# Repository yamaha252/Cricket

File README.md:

# Cricket

Лёгкий BLE-маячок для поиска упавшего FPV-дрона (`cricket-tag`), своё приложение для поиска и, на следующем этапе, приёмник для поискового дрона (`cricket-seeker`).

Маячок спроектирован с нуля на модуле Insight SiP ISP2454-LX (Nordic nRF54L15, D-29). Схема и плата готовы, прошивка и приложение написаны и собираются; платы ещё не заказаны, поэтому на железе ничего не проверено.

## Что умеет cricket-tag

- Ставится на дроны от BetaFPV Pavo Pico II (80 мм) и крупнее, весит около 3 г с аккумулятором.
- Заряжается от 5 В полётника, после падения работает от своего Li-Po: бипер часами, BLE по расчёту 3,5–6,5 недели (ток ещё не измерен).
- Сам отличает падение от замены аккумулятора: статус armed по MSP, удар по акселерометру, нарастающая тревога. Тревогу поднимает и аварийный конец полёта при живых 5 В: failsafe, дизарм в воздухе, перезагрузка полётника, потеря связи с пультом (D-35, D-36).
- Пищит с тумблера BEEPER в Betaflight и по команде из приложения; пока маячок в тревоге, команду «пищи» принимает и чужой телефон — помощник может найти дрон по звуку.
- Виден своему приложению на сотни метров: Coded PHY, ориентир 300–500 м при прямой видимости, на 1M — 150–250 м (D-17). В рекламе — последние координаты GPS полётника и их возраст.
- Молчит в эфире, пока дрон armed, чтобы не мешать ELRS 2,4 ГГц (D-37).
- Громкий бипер уровня Flywoo Finder V1.0 и белый светодиод.
- Обновляется по BLE (MCUboot, подписанные образы), управляется только привязанным телефоном.
- Собирается на заводе целиком, руками только прошивка и пайка проводов аккумулятора и полётника к площадкам (D-26).

Сети Apple Find My и Google Find Hub — следующий этап после своего механизма поиска (D-32, D-33), сейчас их нет ни в прошивке, ни в приложении.

## Схема и плата

Ревизия A: 17 × 32 мм, 2 слоя, 0,6 мм, все детали сверху. Подробности — в [hardware/cricket-tag/README.md](hardware/cricket-tag/README.md).

Слева направо: верх, низ с площадками проводов и SWD, медь обоих слоёв. Модуль ISP2454-LX (вверху слева, у антенны) и излучатель (большой прямоугольник внизу) на рендере не показаны: у них нет 3D-моделей, видны только площадки.

## Документация

| Документ | Содержание |
|---|---|
| [docs/requirements.md](docs/requirements.md) | требования |
| [docs/decisions.md](docs/decisions.md) | журнал решений с причинами (D-1…D-41) |
| [docs/concept.md](docs/concept.md) | архитектура, режимы, признаки падения, радио, энергобюджет |
| [docs/protocol.md](docs/protocol.md) | реклама Cricket, интервалы по режимам, сервис GATT, команды, привязка |
| [docs/components.md](docs/components.md) | компоненты, коды LCSC, номиналы, требования к антенне, масса |
| [docs/manufacturing.md](docs/manufacturing.md) | заводская сборка, варианты заводов, порядок заказа |
| [docs/cost.md](docs/cost.md) | себестоимость: расчёты заводов и оценка по тиражам |
| [docs/module-options.md](docs/module-options.md) | радиомодули со склада JLCPCB и голый nRF54L10 (отклонены) |
| [docs/app.md](docs/app.md) | своё приложение, сети Find My и Find Hub |
| [docs/setup.md](docs/setup.md) | окружение разработки |

## Состав репозитория

| Папка | Назначение | Статус |
|---|---|---|
| [`hardware/cricket-tag/`](hardware/cricket-tag/README.md) | KiCad-проект маячка | схема ревизии A (ERC 0) и плата 17 × 32 мм (DRC 0) готовы и прошли ревью (D-40, D-41); выходные файлы для завода — в `fab/` |
| [`hardware/cricket-seeker/`](hardware/cricket-seeker/README.md) | приёмник для поискового дрона | не начат |
| [`firmware/`](firmware/README.md) | своя прошивка под MIT, Zephyr / nRF Connect SDK v3.4.2 | свой механизм поиска написан, собирается под плату и nRF54L15 DK; на железе не запускалась |
| [`app/`](app/README.md) | приложение на Flutter: Android и iOS | сканер, «тепло-холодно», карта с пеленгом, офлайн-карты, привязка и настройки есть; с настоящим маячком не проверено |
| `docs/` | документация | актуальна |

## Статус

На 2026-11-12.

**Плата.** Схема и плата ревизии A готовы: ERC 0, DRC со сверкой со схемой 0, разводка убрана и проверена (D-40, D-41). Gerber, BOM и CPL делает `hardware/cricket-tag/make_fab.sh`.

**Заказ.** Завод для первого заказа не выбран (D-31), ничего не оплачено. Рекомендованная нулевая партия — 3–4 платы. Расчёты, прошедшие проверку заводов:

| Завод | Партия | К оплате |
|---|---|---|
| SCSPCBA | 4 платы | 159,83 $ |
| NextPCB | 8 плат | 371 $ |
| Seeed Fusion | 8 плат | 520,70 $ (~470 $ с купоном) |

JLCPCB (~250–285 $ за 8 плат) скрывает сборку для Казахстана и делает панели только с V-cut, который плате не подходит. В серии оценка ~20–22 $ за плату при 24 шт. и ~15–17 $ при 120 шт. Подробности — [docs/manufacturing.md](docs/manufacturing.md#варианты-заводов) и [docs/cost.md](docs/cost.md).

**Прошивка.** Наборы рекламы Cricket Coded и 1M, сервис GATT, режимы, бипер, кнопка, клиент MSP, удар по LIS2DH12, привязка, настройки Bluetooth из приложения, MCUboot с обновлением по BLE, сторожевой таймер, сборка с низким потреблением. Не сделано: замер тока, шлюз Bluetooth → MSP для Betaflight Configurator, наборы Apple и Google ([firmware/README.md](firmware/README.md#не-сделано)).

**Приложение.** Свой BLE-слой на Kotlin и Swift, всё работает без сети. Не сделано: обновление прошивки по BLE, фоновое сканирование, сети Find My и Find Hub, подпись сборок ([app/README.md](app/README.md#не-сделано)).

**Дальше:** выбрать завод и заказать платы, проверить прошивку на nRF54L15 DK, затем на плате вместе с приложением, измерить ток.

## Лицензия

[MIT](LICENSE): схема, плата, скрипты, прошивка, приложение и документация.

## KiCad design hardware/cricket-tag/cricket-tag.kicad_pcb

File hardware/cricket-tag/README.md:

# cricket-tag

KiCad-проект маячка. Готовы библиотека проекта и схема ревизии A на модуле ISP2454-LX (D-29; ERC: 0 ошибок, 0 предупреждений). Плата 17 × 32 мм разведена полностью, убрана (D-40) и прошла ревью схемы и разводки (D-41): DRC со сверкой со схемой — 0 нарушений, 0 неподключённых, вся земля связна. Как она разведена — раздел «Разводка», картинки текущей платы — `render/`: [схема](render/schematic.png), [верх](render/3d-top.png), [низ](render/3d-bottom.png), [медь](render/copper-top-bottom.png). Картинки платы — `kicad-cli pcb render --side top|bottom` и `kicad-cli pcb export svg` слоёв F.Cu и B.Cu. Картинку схемы после правок пересобирают: `kicad-cli sch export pdf` с `--exclude-drawing-sheet`, затем `pdftoppm -png -r 130 -singlefile`. Минимумы DRC под JLCPCB 2 слоя (дорожка 0,1 мм, зазор 0,127 мм, via от 0,45/0,3 мм с кольцом 0,1 мм, медь до кромки 0,2 мм; классы цепей — в разделе «Разводка»), стек 0,6 мм FR4, ENIG.

## Параметры платы, ревизия A

- 17 × 32 мм (см. «Размер платы» и «Разводка», D-29), 2 слоя, 0,6 мм.
- Все компоненты сверху, плата собирается заводом целиком. Снизу только медные площадки под провода и SWD (D-26): [docs/manufacturing.md](../../docs/manufacturing.md).
- Модуль Insight SiP ISP2454-LX (nRF54L15, D-29) в углу платы на дальнем конце от хвоста, антенной половиной к торцу: в 1 мм от торцевой кромки и в 1,3 мм от боковой (datasheet: 1 мм; +0,3 мм под дорожки VDD и SWD). У торца полоса 14 × 5 мм без меди на обоих слоях. Подробности в [docs/components.md](../../docs/components.md#требования-к-встроенной-антенне).
- Аккумулятор снизу, до 15 мм длиной вместе с платой защиты, провода паяются к J2.

## Порядок работы над схемой

1. ~~Символ и футпринт модуля~~ — готово: ISP2454-LX (D-29), см. раздел «Библиотека».
2. ~~Вход 5 В, VIN_SENSE, TP4054, площадки аккумулятора, делитель VBAT, LDO~~ — готово, см. раздел «Схема». Площадки полётника J1 нарисованы здесь же, резисторы UART — на шаге 6.
3. ~~Модуль, площадки SWD~~ — готово, карта выводов ниже (D-29). Кварц и развязка модуля с D-29 внутри ISP2454-LX. TC2030-NL заменён четырьмя площадками J3 (D-26).
4. ~~PAM8904E и излучатель~~ — готово, излучатель CPT-1117-83 (D-27), см. «Размер платы».
5. ~~Светодиод с ключом от VBAT, кнопка, LIS2DH12~~ — готово, см. «Схема».
6. ~~Резисторы 1 кОм в UART между площадками полётника и модулем~~ — готово.
7. ~~Поле `LCSC Part` в каждом символе~~ — заполнено у всех деталей в BOM: 20 уникальных позиций (после D-29 ушли кварц и конденсаторы 18 пФ). Без него только площадки J1–J3 (`in_bom no`).
8. ~~ERC до нуля ошибок~~ — 0 ошибок, 0 предупреждений.

Плата с ISP2454-LX разведена (см. «Разводка»). Выходные файлы делает `make_fab.sh` (в `fab/`), по ним 2026-11-10 получены расчёты JLCPCB (D-30) и NextPCB (D-31), см. [docs/cost.md](../../docs/cost.md). После уборки меди D-40 (2026-11-12) gerber изменились, BOM и CPL прежние: перед оплатой любого из расчётов загрузить новый `cricket-tag-gerbers.zip`. Завод для первого заказа не выбран, варианты сравниваются ([docs/manufacturing.md](../../docs/manufacturing.md#варианты-заводов)). Медь местами ближе 0,4 мм к краю, поэтому панель только с фрезеровкой и mouse bites, не V-cut; разделяет завод (D-31).

Компоненты: [docs/components.md](../../docs/components.md). Заметки по схеме: [docs/concept.md](../../docs/concept.md#заметки-для-схемы).

## Схема

`cricket-tag.kicad_sch` строит скрипт `gen_schematic.py` по шагам из списка выше. Каждый вывод подключён коротким проводом к метке цепи или к символу питания. Источник схемы — скрипт: ручные правки в KiCad пропадут при следующем запуске. Когда схема будет готова и её начнут править в KiCad, файл схемы станет основным, а скрипт — историей.

```bash
python3 hardware/cricket-tag/gen_schematic.py
kicad-cli sch erc hardware/cricket-tag/cricket-tag.kicad_sch -o /tmp/erc.rpt
```

Если в KiCad не настроены глобальные таблицы библиотек (их создаёт первый запуск KiCad), ERC сообщает «library not included». Тогда ERC запускают с переменной `KICAD_CONFIG_HOME`: она указывает на каталог `10.0/` с копиями `sym-lib-table` и `fp-lib-table` из `/Applications/KiCad/KiCad.app/Contents/SharedSupport/template/`.

Узел питания (шаг 2):

| Цепь | Что на ней |
|---|---|
| +5V | J1.1 (полётник), анод D1 B5819W, верх делителя VIN_SENSE |
| VCHG | катод D1, C1 10 мкФ, TP4054 VCC |
| VBAT | TP4054 BAT, C2 1 мкФ, J2.1 (аккумулятор), делитель VBAT, вход и EN LDO, C4 1 мкФ |
| +3V3 | выход TPS7A0233, C5 1 мкФ |
| VIN_SENSE | R1 1 МОм / R2 1,5 МОм (D-23) → GPIO модуля |
| VBAT_SENSE | R4 / R5 по 1 МОм, C3 100 нФ → АЦП модуля |
| CHRG_N | открытый сток TP4054 → GPIO с внутренней подтяжкой |
| PROG | R3 22 кОм: ток заряда ≈ 45 мА |

Модуль (шаг 3, D-29): U1 ISP2454-LX — кварцы 32 МГц и 32,768 кГц, DC/DC и развязка VDD внутри модуля, поэтому C6–C9 и Y1 из прежней схемы нет (позиционные обозначения не перенумерованы). Площадки SWD J3: 1 VDD, 2 SWDIO, 3 SWCLK, 4 GND (только медь снизу, `in_bom no`, D-26). OUT_MOD соединён с OUT_ANT; ~RESET (подтяжка внутри) и неиспользуемые GPIO помечены «не подключено».

Карта выводов модуля (D-29):

| Площадка | Порт | Цепь | Примечание |
|---|---|---|---|
| 32 | P0.02 | UART_TX | UARTE30 → RX полётника через 1 кОм (шаг 6) |
| 29 | P0.00 | UART_RX | UARTE30 ← TX полётника через 1 кОм. **Внутренняя** площадка: переходное под модулем, закрытое маской |
| 34 | P0.03 | VIN_SENSE | есть ли 5 В (цифровой вход, D-23), пробуждение из System OFF |
| 36 | P1.07/AIN3 | VBAT_SENSE | АЦП |
| 38 | P1.05 | BUTTON | кнопка на GND, внутренняя подтяжка, пробуждение |
| 40 | P1.04 | BUZ_DIN | PWM20, 3–8 кГц на PAM8904E |
| 42 | P2.05 | BUZ_EN1 | режим PAM8904E |
| 44 | P2.04 | CHRG_N | внутренняя подтяжка; читается опросом (на P2 нет прерываний) |
| 48 | P1.11 | ACC_INT1 | прерывание LIS2DH12, пробуждение. Проведён заранее: переходное справа от модуля, нижний слой под модулем, переходное у U5, сверху к INT1 |
| 2 | P1.02/NFC1 | I2C_SDA | NFC-вывод в режиме GPIO |
| 4 | P1.03/NFC2 | I2C_SCL | NFC-вывод в режиме GPIO, «тактовый» (SCL можно только на такой) |
| 46 | P2.02 | LED | затвор 2N7002; по каналу под модулем к R9 и Q1 |
| 6 | P2.01 | — | свободен (сбоку модуля; LED отсюда пересекал I2C) |
| 26, 28, 30 | VDD, SWDIO, SWDCLK | +3V3, SWDIO, SWDCLK | вдоль левой кромки, дальше на J3 |

Между наружными площадками модуля 0,25 мм: дорожка между ними не проходит, сигналы — только с наружного ряда, кроме UART_RX. Порты nRF54L15 (datasheet, Pin assignments): на P2 нет прерываний и пробуждения из System OFF; АЦП, PWM20–22, UARTE20/21 и TWIM20/21 — на P1; UARTE30/TWIM30 — на P0; SCL — только на «тактовом» выводе. На наружном ряду P0 — 2 вывода, P1 — 6, а сигналов, которым нужен P0 или P1, девять: поэтому UART_RX с внутренней площадки. GRTC PWM на P0.03 для пищалки не годится — фиксированные 128 Гц. NFC-выводы в прошивке перевести в GPIO (на nRF54L — отключить NFCT, `CONFIG_NFCT_PINS_AS_GPIOS`).

GND модуля: угловые 1, 7, 25, 31 — каждая на своё переходное; внутренние 8 и 21, 23, 24 — дорожками к угловым 7 и 25; центральные 12, 14, 16, 18 не подключены: на двух слоях их не вывести, производитель для неполного набора выводов рекомендует только наружные площадки (datasheet, разд. 4.2).

Пищалка (шаг 4): U4 PAM8904E питается от VBAT, C10 2,2 мкФ на входе. Летающие конденсаторы C11 (CP1–CN1) и C12 (CP2–CN2) по 1 мкФ 25 В, на VOUT C13 и C14 по 1 мкФ 25 В. Выходы VO1 и VO2 дифференциально подключены к BZ1 CPT-1117-83 (D-27). EN2 постоянно на VBAT (D-28), режим задаёт EN1 с модуля: 0 — 1x, 1 — 3x; режима 2x нет. DIN = 0 выключает драйвер (ток 0,008 мкА). Режим 3x допустим только при VIN ≤ 4,5 В, у нас VBAT ≤ 4,2 В. Центральная площадка PAM8904E (13) — на GND.

Светодиод, кнопка, акселерометр (шаг 5): белый D2 KT-0603W от VBAT через R8 220 Ом (≈6 мА при 4,2 В), ключ Q1 2N7002 на GPIO LED, R9 10 кОм держит затвор на земле, пока GPIO не настроен. Кнопка SW1 TS-1088 замыкает BUTTON на GND, подтяжка внутри nRF. U5 LIS2DH12 по I2C с подтяжками R10, R11 10 кОм к +3V3, развязка C15 100 нФ и C16 1 мкФ. CS на VDD_IO — режим I2C. SA0 тоже на VDD_IO: адрес 0x19 и нет тока через внутреннюю подтяжку SA0, которую иначе пришлось бы отключать в прошивке. Вывод 5 (Res) на GND, INT1 → ACC_INT1, INT2 не подключён. В KiCad нет символа LIS2DH12, взят LIS2DE12 из `Sensor_Motion` — та же разводка LGA-12 2 × 2 мм.

UART (шаг 6): R6 1 кОм между FC_TX и UART_RX, R7 1 кОм между UART_TX и FC_RX.

ERC: 0 ошибок, 0 предупреждений. Одно замечание исключено намеренно — `pin_to_pin` между SA0 LIS2DH12 (двунаправленный вывод) и выходом LDO на +3V3. Исключение с пояснением прописывает в `cricket-tag.kicad_pro` сам `gen_schematic.py`, ключ привязан к положению вывода: при переносе U5 он пересчитывается.

### Размер платы

Излучатель — CPT-1117-83 (D-27), посадочное место с лепестками 15,5 × 9 мм. В D-25 его меняли на CPT-9019A (10 × 9 мм), пока плата была 13–14 мм шириной; после отказа от разъёмов (D-26) площади хватило, и он вернулся ценой 2 мм ширины.

Расстановка (`floorplan/floorplan.py`) ставит все детали ревизии A, включая шаги 5–6, по их курятникам на пробную плату, DRC ищет перекрытия. Разводка добавила к `w16b` 1 мм ширины и 2,8 мм длины (D-28).

| Вариант | Размер | Картинка | Что |
|---|---|---|---|
| `w16b` | 16 × 29,2 мм | `floorplan/floorplan-w16b-cpt1117.png` | модуль с антенной впереди, рядом акселерометр, кнопка, светодиод; под модулем кварц, затем CPT-1117-83 лепестками вдоль платы, справа от него драйвер и питание. Провода и SWD снизу (D-26, D-27) |
| `w17b` | 17 × 30,2 мм | — | w16b, раздвинутый на 1 мм в ширину и длину под разводку |
| `w17c` | 17 × 31 мм | — | расстановка по выводам: кварц под XL1/XL2, делители и UART под нижним рядом модуля, конденсаторы драйвера у его выводов, светодиод у ключа |
| `isp_c` — **текущий** | **17 × 32 мм** | — | ISP2454-LX (D-29): расстановка по выводам модуля, светодиод с ключом в углу у торца, акселерометр справа от модуля, драйвер с конденсаторами у выводов, кнопка в хвосте; канал 1,8 мм между модулем и рядом резисторов; по ней разведена плата |
| `w17d` | 17 × 32 мм | — | ANNA-B402: w17c с зоной под модулем выше на 1 мм; по ней была разведена плата D-28 |
| `w14s` | 14 × 29,3 мм | `floorplan/floorplan-w14s.png` | то же с CPT-9019A, драйвер сбоку, питание в хвосте (D-26) |
| `w14` | 14 × 35,9 мм | `floorplan/floorplan-w14.png` | то же с разъёмами JST SH в хвосте, до D-26 |
| `w18s` | 18 × 22,8 мм | `floorplan/floorplan-w18s.png` | излучатель рядом с модулем. Та же площадь, но металл излучателя в ~5 мм от антенны и аккумулятор не длиннее 12 мм; не выбран |
| `isp_a16` | 16 × 29,4 мм | `floorplan/floorplan-isp2454.png` (в середине; слева `w16b`) | кандидат: ISP2454-LX (nRF54L15) вместо ANNA-B402, плотно, как `w16b`. Без кварца и развязки модуля (внутри). Зона без меди у торца 14 × 5 мм |
| `isp_a` | 17 × 29,2 мм | — | то же на 17 мм ширины |
| `isp_b` | 17 × 30,1 мм, торец 10 мм | `floorplan/floorplan-isp2454.png` (справа) | `isp_a` с узким торцом у антенны (10 × 5 мм) по datasheet ISP2454: минус 35 мм² платы |

- 22 × 13 мм не получается: сумма курятников около 420 мм² с разъёмами и ~330 мм² без них, а у такой платы 286 мм². Крупнее всего модуль с полосой без меди у торца (~105 мм²) и излучатель (102 мм²).
- Длину набирают ряды деталей вдоль платы (`isp_c`): модуль с отступом от торца 9 мм, канал и ряд резисторов под ним ~5 мм, излучатель с лепестками 16 мм, хвост с кнопкой 2 мм. Питание и драйвер стоят в колонке справа от излучателя и длины не добавляют.
- Аккумулятор лежит снизу и не должен заходить под антенну и модуль: металл оболочки расстраивает антенну. На плате 32 мм перед ним стоят площадки проводов, поэтому аккумулятор не длиннее 15 мм вместе с платой защиты: 401012 (~40 мА·ч) или 401015 (~50 мА·ч).
- Акселерометр по длине ничего не занимает: он стоит в полосе рядом с модулем, которая есть в любом случае.

Площадки J1 (полётник: 1 — 5 В, 2 — GND, 3 — TX полётника, 4 — RX полётника) и J2 (аккумулятор: 1 — плюс, 2 — минус) — только медь снизу, `in_bom no` (D-26). Цепи подписаны на нижней шелкографии: RX, TX, G, 5V у J1 (TX и RX — выводы полётника), «+» и «−» у J2, V (3,3 В), IO, CK, G у J3.

## Разводка

Плату строит и разводит `route.sh` (D-28). Он перезаписывает `cricket-tag.kicad_pcb`, ручные правки платы в KiCad при этом пропадут.

```bash
FREEROUTING=/path/to/freerouting-2.5.0.jar sh hardware/cricket-tag/route.sh
```

Шаги:

1. `gen_pcb.py` — детали из списка соединений схемы по расстановке `floorplan/floorplan.py` (вариант `isp_c`, D-29; до этого `w17d`), контур, подписи площадок снизу. Закреплённые заранее: вывод из-под модуля (`module_escape`, см. ниже) и обвязка PAM8904E (`driver_ground`, `driver_routes`, см. ниже).
2. `export_dsn.py` — Specctra DSN. С D-29 без `--planes`: GND разводится как обычная цепь. С `--planes` Freerouting считал нижний слой сплошной землёй, ставил к каждой площадке GND переходное и сам же резал этот слой дорожками — нижняя земля под модулем оказывалась отрезанной от остальной, а DRC показывал это только как «зона — зона».
3. Freerouting 2.5 без интерфейса, 150 проходов. Нужна Java 25+: стоит OpenJDK из Homebrew (`/opt/homebrew/opt/openjdk/bin/java`), системная Java 21 не подходит.
4. `import_ses.py` — разводка обратно в плату, заливки GND на обеих сторонах; `cleanup.py` — висящие обрывки.
5. Доводка по отчёту DRC, до четырёх кругов: `autofix.py` разбирает отчёт, `maze.py` (A* по сетке 0,05 мм на двух слоях) прокладывает оставшиеся пары площадок, а цепь, которая парой не легла, снимает (`ripup.py`) и прокладывает заново целиком; одиночные GND отводит на переходное `fanout.py`. `connect.py repair` сращивает обрывы Freerouting.
6. `widen.py` — сужения Freerouting у площадок до 0,1 мм; `stitch.py` — ~130 переходных GND сшивают заливки; `cleanup.py --gnd-vias` убирает те, что остались без второй стороны.
7. `tidy.py` — уборка (D-40): `gnd` снимает дорожки GND, лежащие внутри заливки, `dust` — пыль из отрезков внутри площадок, `merge` склеивает микросегменты и спрямляет лесенки до 0/45/90°, `widen` расширяет тонкие дорожки до 0,15 мм, где есть зазор, `vias` ставит второе переходное островкам заливки, которые держатся на одном (D-41).
8. DRC.

Freerouting от запуска к запуску даёт разное (порядок деталей в DSN зависит от их UUID), поэтому доводка выбирается по DRC, а не списком. В одном проходе `route.sh` обычно остаётся 1–3 замечания, каждый раз разных; автоматически они до нуля не сходятся.

Плата в репозитории (D-29, ISP2454-LX) — лучший из ~25 проходов `route.sh`, в котором остались неразведёнными две связи драйвера, BUZ_CP2 (U4.11 → C12.1) и BUZ_P (U4.7 → BZ1.1); их довёл `finish_driver.py` (ниже), затем `stitch.py` и `cleanup.py --gnd-vias`. Итог: DRC со сверкой со схемой — 0 нарушений, 0 неподключённых, все 35 площадок GND в одной земле.

Уборка D-40 (2026-11-12) сделана на этой же плате, без повторной трассировки: `tidy.py` снял 119 из 126 незакреплённых дорожек GND, отрезков стало 329 вместо 657. DRC после неё — 0 нарушений и 0 предупреждений при `--severity-all`.

Ревью D-41 добавило два переходных GND: второе в островок земли акселерометра и C10 и второе внутри J2.2 — минус батареи снизу зажат дорожками и раньше выходил на землю через одно отверстие в центральной площадке драйвера.

Площадки под ручную пайку J1 и J2 (D-40): чужая медь не ближе 0,3 мм. Заливку держат зоны без заливки `wire-pads-J1`, `wire-pads-J2` на нижнем слое (`gen_pcb.wire_pad_keepouts`), дорожки и переходные — правило `wire_pad_clearance` в `cricket-tag.kicad_dru`; `maze.py`, `stitch.py` и `tidy.py` учитывают тот же зазор (`gen_pcb.WIRE_PAD_GAP`). Между площадками 0,8 мм: дорожка 0,15 мм проходит только по середине. `export_dsn.py` этот зазор Freerouting не передаёт, после `route.sh` его нарушения покажет DRC, править их вручную.

Обвязка драйвера (`gen_pcb.py`, `DRIVER_TRACKS`, `DRIVER_VIAS`) закреплена заранее, потому что Freerouting её не находит. По кругу выводы PAM8904E идут 12 VBAT, 11 CP2, 10 VOUT, 9 CP1, 8 CN2, 7 OUTP: CP2 к C12 и CP1 к C11 в один слой не развести, а снизу под драйвером лежат площадки батареи J2, так что переходные встают только вокруг них:

- CP2 с вывода 11 идёт дорожкой 0,12 мм по диагонали между углом C10.2 и выводом 10 (щель 0,41 мм) к переходному между C10 и C13, по низу — к переходному над C12;
- C13 и C14 ради этого переходного сдвинуты на 0,15 мм вправо (`floorplan.py`, `isp_c`);
- VOUT идёт по диагонали к C13 и C14;
- CP1 уходит переходным над правым верхним углом J2.1 (место одно: между дорожкой VOUT, площадкой C12.1, переходным CP2 и зазором 0,3 мм до J2.1) и по низу справа от J2 к переходному у C11;
- переходное центральной площадки (GND) стоит у её левого края и снизу соединено дорожкой с J2.2: между площадками батареи меди нет (D-40);
- VBAT вывода 12 через переходное у вывода 1 выходит прямо на J2.1; прежняя связь J2.1 с верхним VBAT по низу через x = 114 мм стала лишней и снята, потому что пересекала CP2;
- OUTP идёт к переходному справа от C12, дальше к излучателю её разводит Freerouting или `maze.py`.

`finish_driver.py` ставит эту обвязку на уже разведённую плату, не трогая остальное:

1. Сдвигает C13 и C14 вместе с концами их дорожек.
2. Снимает старую разводку цепей обвязки и пересекавшие её незакреплённые дорожки.
3. Ведёт OUTP от переходного к BZ1.1 через `maze.py`. Дорожки GND лабиринт может пересечь за штраф (`SOFT_COST`), а те, что пересёк, снимаются: землю держат заливки.
4. Снимает висящие обрывки, в том числе два лишних переходных SWDIO и SWDCLK у левой кромки.

После него нужны `stitch.py` и `cleanup.py --gnd-vias`: заливка в одном кармане над J1 (R2.2) теряла связь, пока не встало сшивающее переходное. `maze.py` с D-29 спрямляет путь по прямой видимости, без ступенек сетки.

Вывод из-под модуля (`gen_pcb.py`, `ESCAPE_TRACKS`) закреплён заранее: VDD, SWDIO, SWDCLK по полосе 1,3 мм у левой кромки на переходные; UART_RX с внутренней площадки 29 на переходное под модулем; ACC_INT1 с площадки 48 через два переходных и нижний слой под модулем к INT1 акселерометра; угловые GND 25, 7, 31 на свои переходные; внутренние GND 8 и 21–24 к угловым; OUT_MOD ↔ OUT_ANT.

Ход перебора D-29 и что не сработало: закреплённая разводка драйвера, скопированная со старой платы (ломает соседние цепи и требует переноса J2; сработала обвязка, нарисованная заново под J2, см. выше), смена порядка в `maze.py`, `stitch.py`-подобная сшивка островков. Повторный `route.sh` даёт каждый раз другое, обычно 3–10 неразведённых. С закреплённой обвязкой драйвера пять проверочных проходов с нуля (2026-11-10) дали 4–8 неподключённых площадок, обвязка и OUTP легли во всех; оставались VBAT (питание R8, U2, R4), SWDIO/SWDCLK к J3, I2C — их доводят вручную или `maze.py`.

Повторно запускать `route.sh` стоит только при изменении схемы или расстановки: он перезапишет плату, и доводку придётся проверить заново. Мелкие правки удобнее делать прямо в KiCad.

Правила (D-28, JLCPCB, 2 слоя): сигналы 0,15 мм с зазором 0,13 мм, питание 0,25 мм, переходные 0,5/0,3 и 0,6/0,3 мм, зазор отверстие — медь 0,2 мм, отверстие — отверстие 0,25 мм, медь до края 0,2 мм.

## Библиотека

Библиотека `cricket` подключена к проекту через `sym-lib-table` и `fp-lib-table` с путём `${KIPRJMOD}/lib/`. Пользовательские символы, футпринты и 3D-модели кладутся туда же.

| Элемент | Что это |
|---|---|
| `cricket:ISP2454-LX` | символ модуля (D-29). Выводы названы по портам nRF54L15 (`P1.04/AIN0`), номер вывода — номер площадки модуля. Справа все GPIO по портам, слева питание, ~RESET, SWD, OUT_MOD/OUT_ANT, внизу 12 GND отдельными выводами (центральные 12–18 на схеме «не подключено»), механические 49–62 скрыты. Поле `LCSC Part` = C44975104 |
| `cricket:ISP2454-LX_CornerAntenna`, `cricket:ISP2454-LX_NarrowEnd` | футпринты модуля: площадки по библиотеке Eagle производителя, зона без меди и курятник до кромки по datasheet разд. 4.3 — в углу платы (боковая кромка в 1,3 мм) и для торца 10 мм |
| `cricket:ANNA-B402` (до D-29) | символ модуля. Выводы названы по портам nRF52833 (`P0.20`), номер вывода — номер площадки модуля. Справа все GPIO, слева питание, SWD, кварц, антенна и USB, внизу GND (11 выводов в одной точке). Поле `LCSC Part` = C6124130 |
| `cricket:TP4054`, `cricket:TPS7A0233`, `cricket:PAM8904E`, `cricket:VBAT` | зарядка, LDO, драйвер пищалки и символ питания VBAT; их генерирует `lib/gen_symbols.py` |
| `cricket:Diodes_W-QFN2020-12_2x2mm_P0.4mm_EP1.0x1.0mm`, `cricket:SameSky_CPT-9019A-SMT`, `cricket:SameSky_CPT-1117-83-SMT` | футпринты PAM8904E и излучателей (стоит CPT-1117-83, CPT-9019A — запасной, D-27) по рекомендованным рисункам площадок производителей; их генерирует `lib/gen_footprints.py` |
| `cricket:WirePads_1x04_P2.0mm`, `cricket:WirePads_1x02_P2.0mm`, `cricket:SWD_Pads_1x04_P2.54mm` | площадки под провода (1,2 × 2,0 мм, шаг 2 мм) и SWD (круглые 1,2 мм, шаг 2,54 мм) для нижней стороны: без пасты, исключены из BOM и CPL (D-26); тоже из `lib/gen_footprints.py` |
| `cricket:ANNA-B402_CornerAntenna` (до D-29) | футпринт: 56 площадок по рис. 5 datasheet, противовес на выводе 1 (медь под маской), зона запрета дорожек, via и заливки на F.Cu и B.Cu по рис. 33–34 руководства u-blox. Положение кромок, как у u-blox, отмечено на Cmts.User |

Символ и футпринты ISP2454-LX генерирует `lib/gen_isp2454.py`, там же источники размеров. Правки нужно вносить в скрипт: ручные правки в редакторе KiCad пропадут при следующем запуске. Дорожка или via в антенной зоне дают ошибку DRC `items_not_allowed`.

Сверка с datasheet isp_ble_DS2454 R7 (2026-11-10): назначение всех 62 площадок и их положение совпадают с таблицей раздела 3 и чертежом раздела 4.1. Размеры площадок взяты из библиотеки Eagle производителя и отличаются от чертежа R7 не больше чем на 0,05 мм: в футпринте сигнальные 0,4 × 0,4 мм и угловые 0,8 × 0,8 мм, на чертеже наружные 0,4 × 0,35 мм, угловые 0,75 × 0,75 и 0,8 × 0,75 мм, центры угловых и нижних механических смещены на 0,025 мм. Допуск чертежа ±0,03 мм, зазор 0,25 мм между площадками сохраняется, плата не менялась.

На схеме с ISP2454-LX:

- OUT_MOD (22) соединить с OUT_ANT (20);
- ~RESET (13) и свободные GPIO — «не подключено»;
- механические площадки 49–62 остаются без цепей, но паяются (datasheet, разд. 3).

Символ и футпринт ANNA-B402 (до D-29) генерирует `lib/gen_anna_b402.py`; они оставлены в библиотеке для старых вариантов расстановки и на плате не используются.

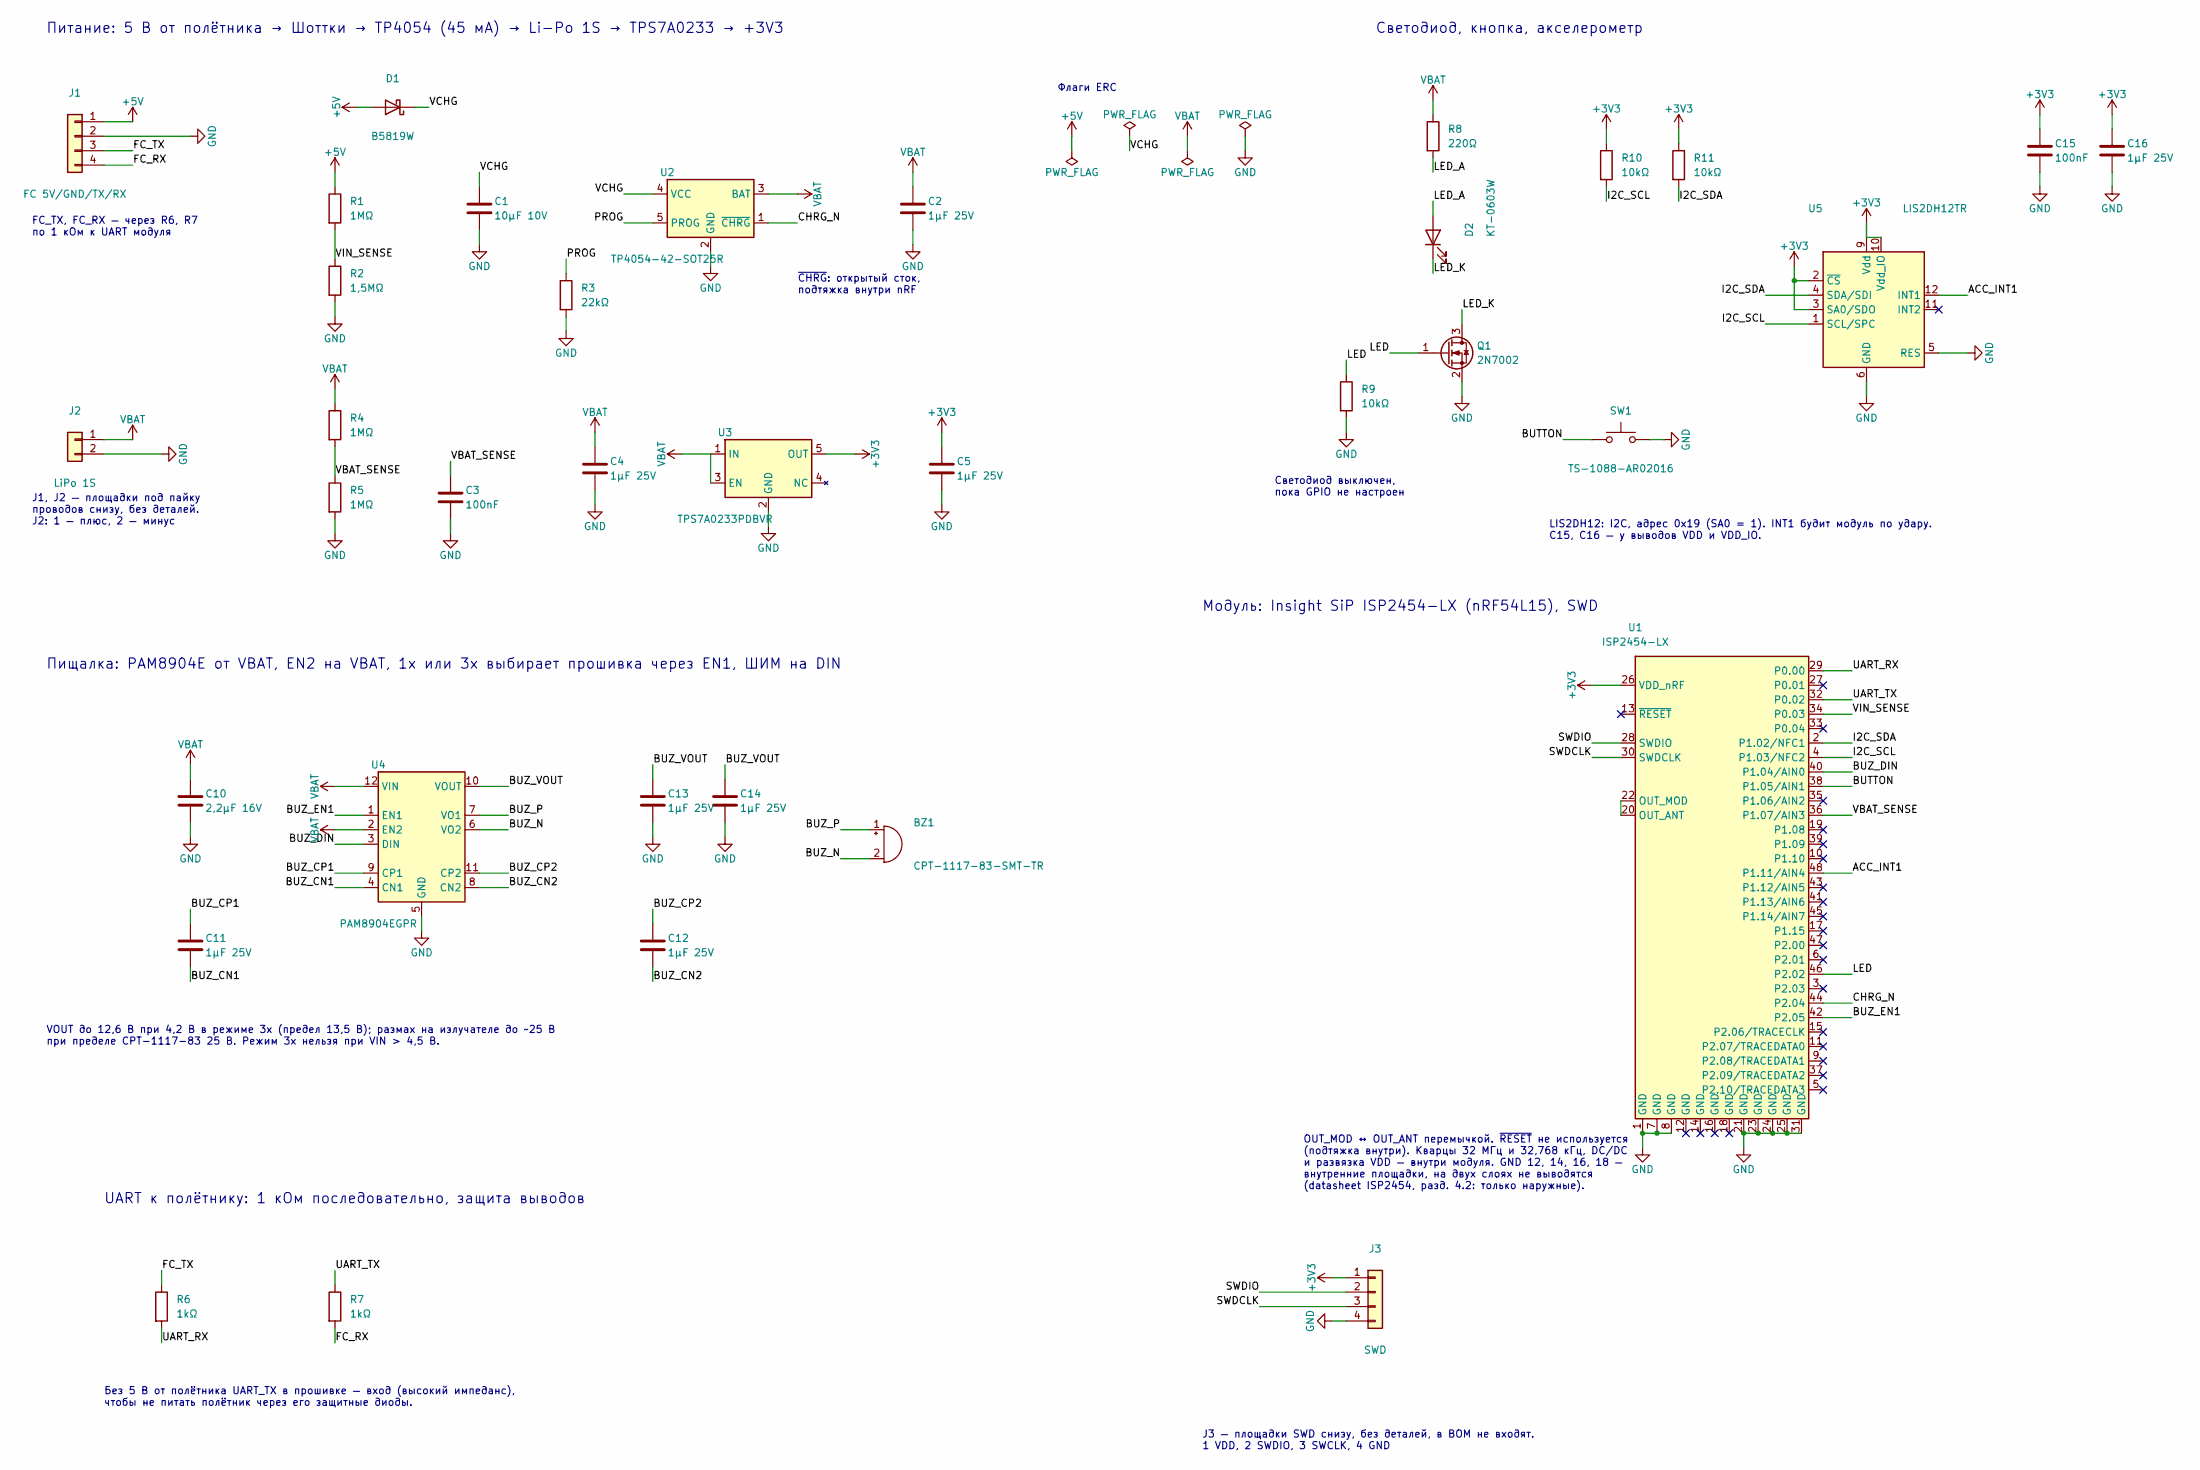
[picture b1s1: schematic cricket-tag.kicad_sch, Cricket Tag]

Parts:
BZ1: CPT-1117-83-SMT-TR; SameSky_CPT-1117-83-SMT; MPN CPT-1117-83-SMT-TR; LCSC Part C22359733
C1: 10µF 10V; C_0603_1608Metric; LCSC Part C19702
C2, C4, C5, C11, C12, C13, C14, C16: 1µF 25V; C_0402_1005Metric; LCSC Part C52923
C3, C15: 100nF; C_0402_1005Metric; LCSC Part C1525
C10: 2,2µF 16V; C_0603_1608Metric; LCSC Part C23630
D1: B5819W; D_SOD-123; LCSC Part C8598
D2: KT-0603W; LED_0603_1608Metric; MPN KT-0603W; LCSC Part C2290
J1: FC 5V/GND/TX/RX; WirePads_1x04_P2.0mm
J2: LiPo 1S; WirePads_1x02_P2.0mm
J3: SWD; SWD_Pads_1x04_P2.54mm
Q1: 2N7002; SOT-23; MPN 2N7002; LCSC Part C8545
R1, R4, R5: 1MΩ; R_0402_1005Metric; LCSC Part C26083
R2: 1,5MΩ; R_0402_1005Metric; LCSC Part C22276
R3: 22kΩ; R_0402_1005Metric; LCSC Part C25768
R6, R7: 1kΩ; R_0402_1005Metric; LCSC Part C11702
R8: 220Ω; R_0402_1005Metric; LCSC Part C25091
R9, R10, R11: 10kΩ; R_0402_1005Metric; LCSC Part C25744
SW1: TS-1088-AR02016; SW_SPST_TS-1088-xR020; MPN TS-1088-AR02016; LCSC Part C720477
U1: ISP2454-LX; ISP2454-LX_CornerAntenna; MPN ISP2454-LX-RS; LCSC Part C44975104
U2: TP4054-42-SOT25R; SOT-23-5; MPN TP4054-42-SOT25R; LCSC Part C32574
U3: TPS7A0233PDBVR; SOT-23-5; MPN TPS7A0233PDBVR; LCSC Part C2887324
U4: PAM8904EGPR; Diodes_W-QFN2020-12_2x2mm_P0.4mm_EP1.0x1.0mm; MPN PAM8904EGPR; LCSC Part C510550
U5: LIS2DH12TR; LGA-12_2x2mm_P0.5mm; MPN LIS2DH12TR; LCSC Part C110926

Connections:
+3V3: C5.1, C15.1, C16.1, J3.1, R10.1, R11.1, U1.26 (VDD_nRF), U3.5 (OUT), U5.2 (~CS), U5.3 (SA0/SDO), U5.9 (Vdd), U5.10 (Vdd_IO)
+5V: D1.2 (A), J1.1, R1.1
/ACC_INT1: U1.48 (P1.11/AIN4), U5.12 (INT1)
/BUTTON: SW1.1, U1.38 (P1.05/AIN1)
/BUZ_CN1: C11.2, U4.4 (CN1)
/BUZ_CN2: C12.2, U4.8 (CN2)
/BUZ_CP1: C11.1, U4.9 (CP1)
/BUZ_CP2: C12.1, U4.11 (CP2)
/BUZ_DIN: U1.40 (P1.04/AIN0), U4.3 (DIN)
/BUZ_EN1: U1.42 (P2.05), U4.1 (EN1)
/BUZ_N: BZ1.2 (-), U4.6 (VO2)
/BUZ_P: BZ1.1 (+), U4.7 (VO1)
/BUZ_VOUT: C13.1, C14.1, U4.10 (VOUT)
/CHRG_N: U1.44 (P2.04), U2.1 (~CHRG)
/FC_RX: J1.4, R7.2
/FC_TX: J1.3, R6.1
/I2C_SCL: R10.2, U1.4 (P1.03/NFC2), U5.1 (SCL/SPC)
/I2C_SDA: R11.2, U1.2 (P1.02/NFC1), U5.4 (SDA/SDI)
/LED: Q1.1 (G), R9.1, U1.46 (P2.02)
/LED_A: D2.2 (A), R8.2
/LED_K: D2.1 (K), Q1.3 (D)
/PROG: R3.1, U2.5 (PROG)
/SWDCLK: J3.3, U1.30 (SWDCLK)
/SWDIO: J3.2, U1.28 (SWDIO)
/UART_RX: R6.2, U1.29 (P0.00)
/UART_TX: R7.1, U1.32 (P0.02)
/VBAT_SENSE: C3.1, R4.2, R5.1, U1.36 (P1.07/AIN3)
/VCHG: C1.1, D1.1 (K), U2.4 (VCC)
/VIN_SENSE: R1.2, R2.1, U1.34 (P0.03)
GND: C1.2, C2.2, C3.2, C4.2, C5.2, C10.2, C13.2, C14.2, C15.2, C16.2, J1.2, J2.2, J3.4, Q1.2 (S), R2.2, R3.2, R5.2, R9.2, SW1.2, U1.1 (GND), U1.7 (GND), U1.8 (GND), U1.21 (GND), U1.23 (GND), U1.24 (GND), U1.25 (GND), U1.31 (GND), U2.2 (GND), U3.2 (GND), U4.5 (GND), U4.13 (GND), U5.5 (RES), U5.6 (GND), U5.7 (GND), U5.8 (GND)
unnamed: U1.20 (OUT_ANT), U1.22 (OUT_MOD)
VBAT: C2.1, C4.1, C10.1, J2.1, R4.1, R8.1, U2.3 (BAT), U3.1 (IN), U3.3 (EN), U4.2 (EN2), U4.12 (VIN)

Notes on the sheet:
Питание: 5 В от полётника → Шоттки → TP4054 (45 мА) → Li-Po 1S → TPS7A0233 → +3V3
FC_TX, FC_RX — через R6, R7 по 1 кОм к UART модуля
~{CHRG}: открытый сток, подтяжка внутри nRF
J1, J2 — площадки под пайку проводов снизу, без деталей. J2: 1 — плюс, 2 — минус
Флаги ERC
Модуль: Insight SiP ISP2454-LX (nRF54L15), SWD
OUT_MOD ↔ OUT_ANT перемычкой. ~{RESET} не используется (подтяжка внутри). Кварцы 32 МГц и 32,768 кГц, DC/DC и развязка VDD — внутри модуля. GND 12, 14, 16, 18 — внутренние площадки, на двух слоях не выводятся (datasheet ISP2454, разд. 4.2: только наружные).
J3 — площадки SWD снизу, без деталей, в BOM не входят. 1 VDD, 2 SWDIO, 3 SWCLK, 4 GND
Пищалка: PAM8904E от VBAT, EN2 на VBAT, 1x или 3x выбирает прошивка через EN1, ШИМ на DIN
VOUT до 12,6 В при 4,2 В в режиме 3x (предел 13,5 В); размах на излучателе до ~25 В при пределе CPT-1117-83 25 В. Режим 3x нельзя при VIN > 4,5 В.
Светодиод, кнопка, акселерометр
Светодиод выключен, пока GPIO не настроен
LIS2DH12: I2C, адрес 0x19 (SA0 = 1). INT1 будит модуль по удару. C15, C16 — у выводов VDD и VDD_IO.
UART к полётнику: 1 кОм последовательно, защита выводов
Без 5 В от полётника UART_TX в прошивке — вход (высокий импеданс), чтобы не питать полётник через его защитные диоды.

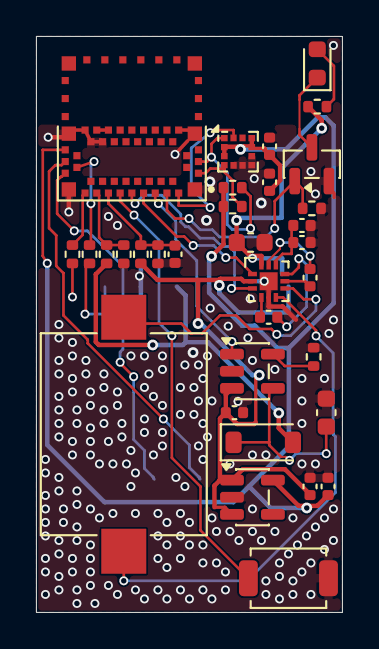
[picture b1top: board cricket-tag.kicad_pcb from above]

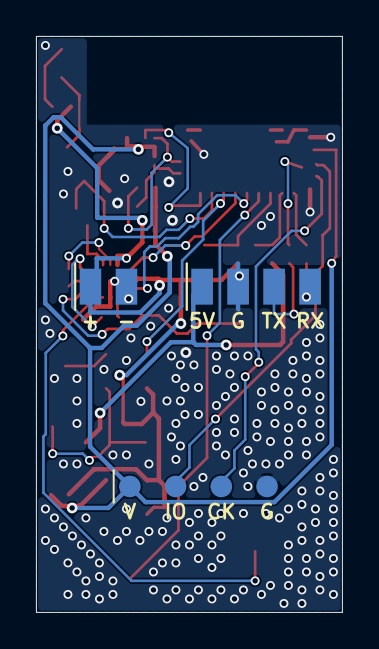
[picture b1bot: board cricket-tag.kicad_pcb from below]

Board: 2 copper layers, 17.0 x 32.0 mm, 36 parts (3 on the bottom side), 32 nets.

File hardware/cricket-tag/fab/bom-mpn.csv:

"Designator","Quantity","Manufacturer","Manufacturer Part Number","Description","Package","LCSC Part #"
"BZ1","1","Same Sky","CPT-1117-83-SMT-TR","CPT-1117-83-SMT-TR","SameSky_CPT-1117-83-SMT","C22359733"
"C1","1","Samsung Electro-Mechanics","CL10A106KP8NNNC","10uF 10V","C_0603_1608Metric","C19702"
"C2,C4,C5,C11,C12,C13,C14,C16","8","Samsung Electro-Mechanics","CL05A105KA5NQNC","1uF 25V","C_0402_1005Metric","C52923"
"C3,C15","2","Samsung Electro-Mechanics","CL05B104KO5NNNC","100nF","C_0402_1005Metric","C1525"
"C10","1","Samsung Electro-Mechanics","CL10A225KO8NNNC","2,2uF 16V","C_0603_1608Metric","C23630"
"D1","1","Changjiang Electronics Tech (CJ)","B5819W SL","B5819W","D_SOD-123","C8598"
"D2","1","Hubei KENTO Elec","KT-0603W","KT-0603W","LED_0603_1608Metric","C2290"
"Q1","1","Changjiang Electronics Tech (CJ)","2N7002","2N7002","SOT-23","C8545"
"R1,R4,R5","3","UNI-ROYAL","0402WGF1004TCE","1MOhm","R_0402_1005Metric","C26083"
"R2","1","UNI-ROYAL","0402WGF1504TCE","1,5MOhm","R_0402_1005Metric","C22276"
"R3","1","UNI-ROYAL","0402WGF2202TCE","22kOhm","R_0402_1005Metric","C25768"
"R6,R7","2","UNI-ROYAL","0402WGF1001TCE","1kOhm","R_0402_1005Metric","C11702"
"R8","1","UNI-ROYAL","0402WGF2200TCE","220Ohm","R_0402_1005Metric","C25091"
"R9,R10,R11","3","UNI-ROYAL","0402WGF1002TCE","10kOhm","R_0402_1005Metric","C25744"
"SW1","1","XUNPU","TS-1088-AR02016","TS-1088-AR02016","SW_SPST_TS-1088-xR020","C720477"
"U1","1","Insight SiP","ISP2454-LX-RS","ISP2454-LX","ISP2454-LX_CornerAntenna","C44975104"
"U2","1","TOPPOWER","TP4054-42-SOT25R","TP4054-42-SOT25R","SOT-23-5","C32574"
"U3","1","Texas Instruments","TPS7A0233PDBVR","TPS7A0233PDBVR","SOT-23-5","C2887324"
"U4","1","Diodes Incorporated","PAM8904EGPR","PAM8904EGPR","Diodes_W-QFN2020-12_2x2mm_P0.4mm_EP1.0x1.0mm","C510550"
"U5","1","STMicroelectronics","LIS2DH12TR","LIS2DH12TR","LGA-12_2x2mm_P0.5mm","C110926"

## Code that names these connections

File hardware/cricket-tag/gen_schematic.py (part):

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    s.connect(d1, 2, "+5V")
    s.connect(d1, 1, "VCHG")

    # Делитель VIN_SENSE: 1 МОм / 1,5 МОм → 2,85–3,15 В на GPIO при 5 В ±5 % (D-23)
    r1 = s.place("Device:R", "R1", 24, 17, "1MΩ", footprint=R0402, lcsc="C26083",
                 ref_at=(1, -0.5), val_at=(1, 0.5))
    r2 = s.place("Device:R", "R2", 24, 22, "1,5MΩ", footprint=R0402, lcsc="C22276",
                 ref_at=(1, -0.5), val_at=(1, 0.5))
    s.connect(r1, 1, "+5V")
    s.connect_pins(r1, 2, r2, 1, "VIN_SENSE")
    s.connect(r2, 2, "GND")

    # TP4054: ток заряда 1000 В / 22 кОм ≈ 45 мА
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    r5 = s.place("Device:R", "R5", 24, 37, "1MΩ", footprint=R0402, lcsc="C26083",
                 ref_at=(1, -0.5), val_at=(1, 0.5))
    s.connect(r4, 1, "VBAT")
    s.connect_pins(r4, 2, r5, 1, "VBAT_SENSE")
    s.connect(r5, 2, "GND")
    cap(s, "C3", 32, 37, "100nF", "C1525", "VBAT_SENSE")

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    44: "CHRG_N",      # P2.04 — открытый сток TP4054, внутренняя подтяжка, опросом
    46: "LED",         # P2.02 — затвор 2N7002, по каналу под модулем к R9 и Q1
    48: "ACC_INT1",    # P1.11 — прерывание LIS2DH12
    2: "I2C_SDA",      # P1.02 (NFC1 → GPIO)
    4: "I2C_SCL",      # P1.03 (NFC2 → GPIO, тактовый вывод)
}
GND_USED = (1, 7, 8, 21, 23, 24, 25, 31)   # 12, 14, 16, 18 — внутренние, не подключаются

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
